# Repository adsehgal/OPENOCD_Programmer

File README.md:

<!--  -->
# ON GOING PROJECT

# *OPENOCD Programmer*

This repo contains project files for a raspberry pi controlled OpenOCD programmer to burn bootloaders to ATMEL SAMD21 MCUs and potentially other microcontrollers.

## *Requirements:*

## Built With

* [KiCad](https://kicad-pcb.org/) - Schematic capture and layout
* [VS Code](https://code.visualstudio.com/) - Used to develop firmware
* [Fusion 360](https://www.autodesk.com/education/edu-software/overview) - Used to design 3-D models for packages

### *Notes:*
- The PCB uses a 5/5mil DRC constraint
- Non-standard footprint 3-D models have been provided in the STEP file format

## Authors

* **Aditya Sehgal** - *PCB Layout, Firmware, 3-D Modelling* - [Adsehgal](https://github.com/adsehgal)

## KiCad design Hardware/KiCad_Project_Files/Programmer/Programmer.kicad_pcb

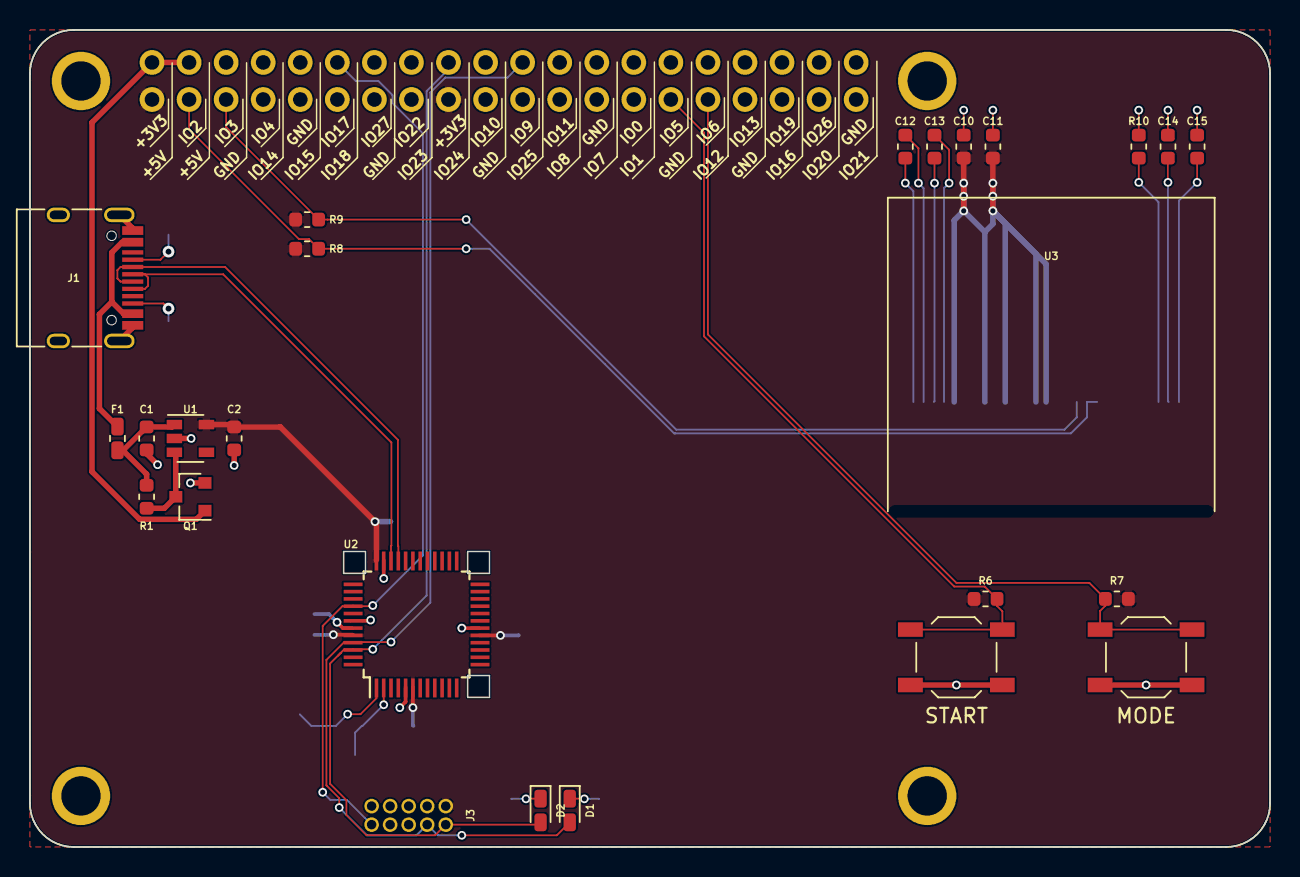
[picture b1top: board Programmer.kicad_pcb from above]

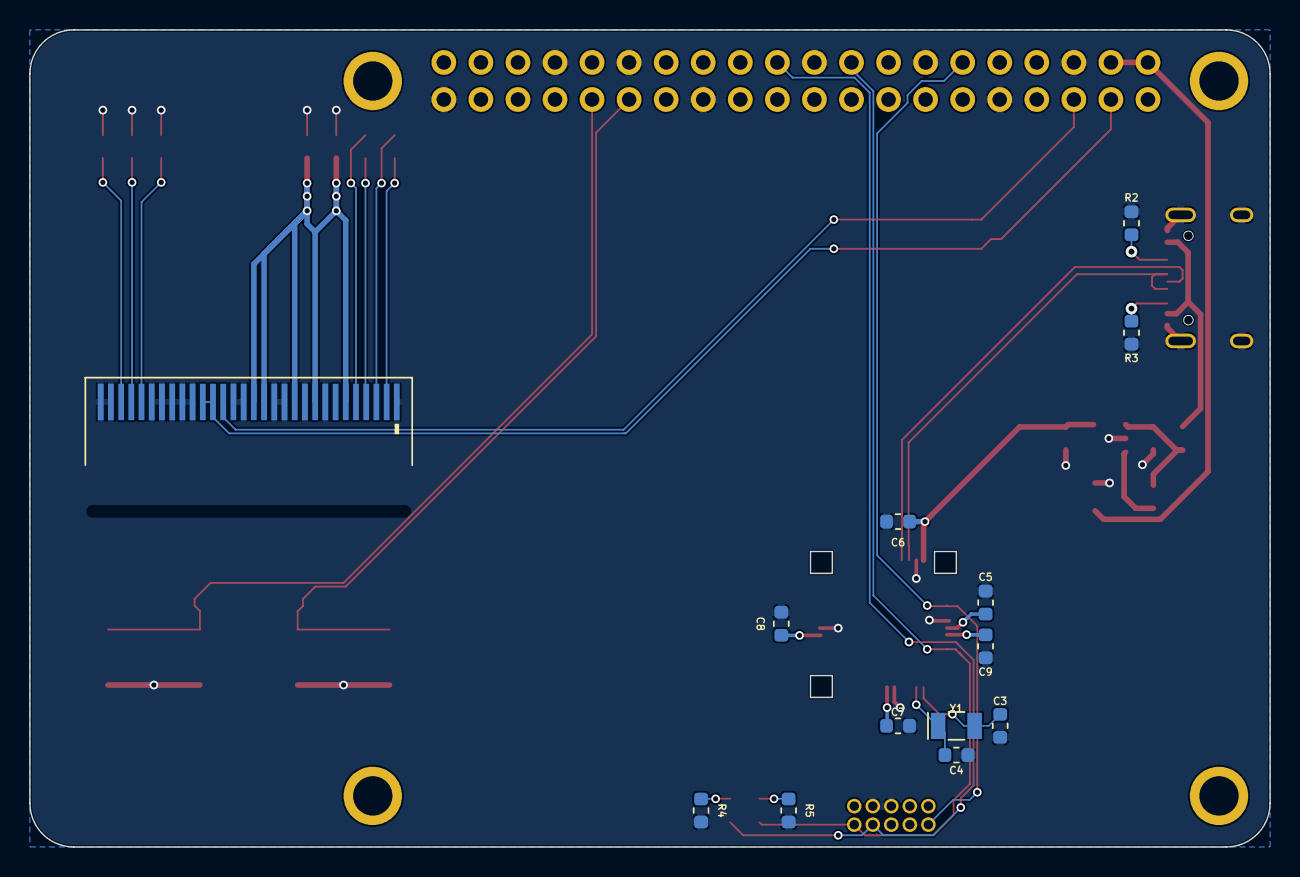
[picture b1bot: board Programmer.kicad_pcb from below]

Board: 2 copper layers, 85.0 x 56.0 mm, 38 parts (12 on the bottom side), 29 nets.

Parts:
C1, C6, C7, C8, C9: 100nF; C_0603_1608Metric
C2, C15: 2.2µF; C_0603_1608Metric
C3, C4: 22pF; C_0603_1608Metric
C5, C10, C11, C12, C13: 1µF; C_0603_1608Metric
C14: 4.7µF; C_0603_1608Metric
D1, D2: LED_Small; LED_0603_1608Metric_Castellated
F1: Fuse_Small; Fuse_0603_1608Metric_Castellated
J1: USB_C_Receptacle_USB2.0; USB_C_Receptacle_HRO_TYPE-C-31-M-12
J2: R_PI_4; PI_4_W_SILK
J3: SWD; PinHeader_2x05_P1.27mm_Vertical
Q1: FDN335N; SOT-23
R1: 10KΩ; R_0603_1608Metric
R2, R3, R10: 5.1KΩ; R_0603_1608Metric
R4, R5, R6, R7: 330Ω; R_0603_1608Metric
R8, R9: 2.2KΩ; R_0603_1608Metric
SW1: START; SW_SPST_TL3342
SW2: MODE; SW_SPST_TL3342
U1: MIC5205-3.3YM5; SOT-23-5
U2: ATSAMD21G18A-A; TQFP-48_7x7mm_P0.5mm
U3: SSD1306_0.96in
Y1: 32.876; Crystal_SMD_EuroQuartz_EQ161-2Pin_3.2x1.5mm

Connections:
+3V3: C2.1, C6.1, C7.1, C8.1, C9.1, C10.1, C11.1, J2.1, J2.17, J3.1, R6.1, R7.1, R8.1, R9.1, U1.5 (OUT), U2.6 (VDDANA), U2.17 (VDDIO), U2.36 (VDDIO), U2.44 (VDDIN), U3.6 (VDDB), U3.9 (VDD), U3.11 (BS1), U3.14 (~RES), U3.15 (D/~C)
+5V: J2.2, J2.4, Q1.1 (G)
/D+: J1.A6 (D+), J1.B6 (D+), U2.34 (PA25)
/D-: J1.A7 (D-), J1.B7 (D-), U2.33 (PA24)
/MODE: J2.31, R7.2, SW2.2
/SCL: J2.5, R9.2, U3.18 (D0)
/SDA: J2.3, R8.2, U3.19 (D1), U3.20 (D2)
/START: J2.29, R6.2, SW1.2
/SWDCLK: D1.2 (A), J2.22, J3.4, U2.45 (PA30)
/SWDIO: D2.2 (A), J2.18, J3.2, U2.46 (PA31)
/~RST: J2.12, J3.10, U2.40 (~RESET)
GND: C1.2, C2.2, C3.1, C4.1, C5.1, C6.2, C7.2, C8.2, C9.2, C10.2, C11.2, C14.1, C15.1, J1.A1 (GND), J1.A12 (GND), J1.B1 (GND), J1.B12 (GND), J1.S1 (SHIELD), J2.6, J2.9, J2.14, J2.20, J2.25, J2.30, J2.34, J2.39, J3.3, J3.5, Q1.2 (S), R2.2, R3.2, R4.2, R5.2, R10.2, SW1.1, SW2.1, U1.2 (GND), U2.5 (GNDANA), U2.18 (GND), U2.35 (GND), U2.42 (GND), U3.1 (GND), U3.8 (VSS), U3.10 (BS0), U3.12 (BS2), U3.13 (~CS), U3.16 (R/~W), U3.17 (E/R~D), U3.21 (D3), U3.22 (D4), U3.23 (D5), U3.24 (D6), U3.25 (D7), U3.29 (VLSS), U3.30 (GND)
unnamed: C3.2, U2.1 (PA00), Y1.2
unnamed: C4.2, U2.2 (PA01), Y1.1
unnamed: C5.2, U2.43 (VDDCORE)
unnamed: C12.1, U3.2 (C2P)
unnamed: C12.2, U3.3 (C2N)
unnamed: C13.1, U3.4 (C1P)
unnamed: C13.2, U3.5 (C1N)
unnamed: C14.2, U3.27 (VCOMH)
unnamed: C15.2, U3.28 (VCC)
unnamed: D1.1 (K), R4.1
unnamed: D2.1 (K), R5.1
unnamed: F1.1, J1.A4 (VBUS), J1.A9 (VBUS), J1.B4 (VBUS), J1.B9 (VBUS)
unnamed: J1.A5 (CC1), R2.1
unnamed: J1.B5 (CC2), R3.1
unnamed: Q1.3 (D), R1.2, U1.3 (EN)
unnamed: R10.1, U3.26 (IREF)
VBUS: C1.1, F1.2, R1.1, U1.1 (IN)

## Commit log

2020-09-08 rename
2020-09-08 PCB init
2020-09-08 schem save
2020-09-11 layout init
2020-09-11 added oled
2020-09-27 layout complete
2020-09-27 fixed zip
